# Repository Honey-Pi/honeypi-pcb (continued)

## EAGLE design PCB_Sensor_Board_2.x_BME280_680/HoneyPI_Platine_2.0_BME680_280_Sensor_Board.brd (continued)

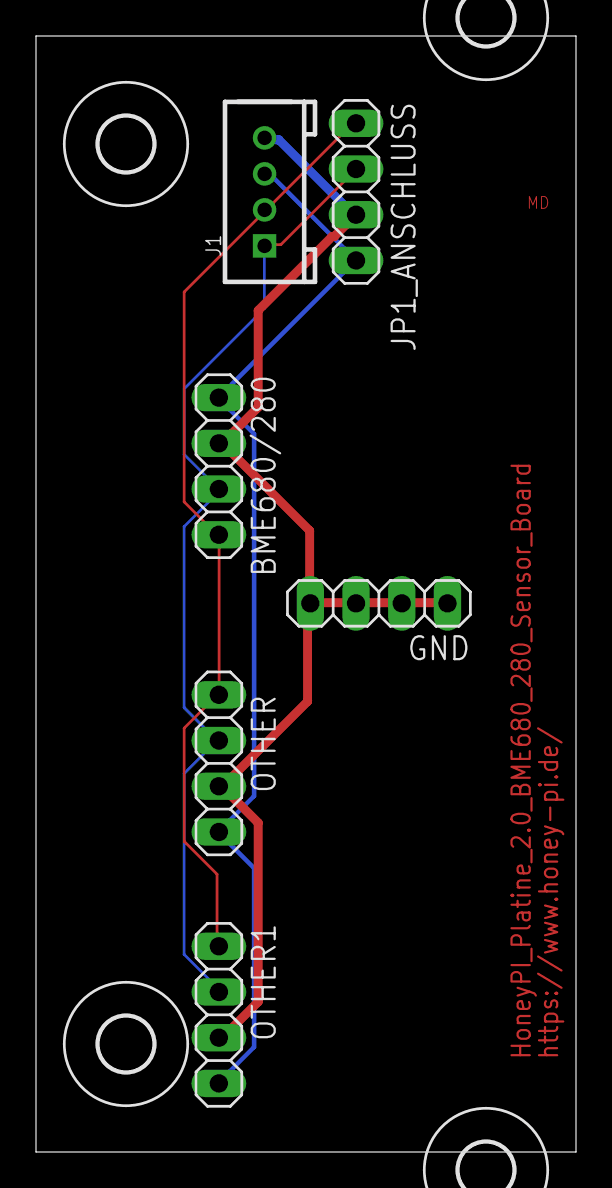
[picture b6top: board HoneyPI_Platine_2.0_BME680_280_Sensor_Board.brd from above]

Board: 2 copper layers, 30.0 x 62.0 mm, 10 parts (0 on the bottom side), 4 nets.

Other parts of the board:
U$1, U$2, U$3, U$4: 3,0

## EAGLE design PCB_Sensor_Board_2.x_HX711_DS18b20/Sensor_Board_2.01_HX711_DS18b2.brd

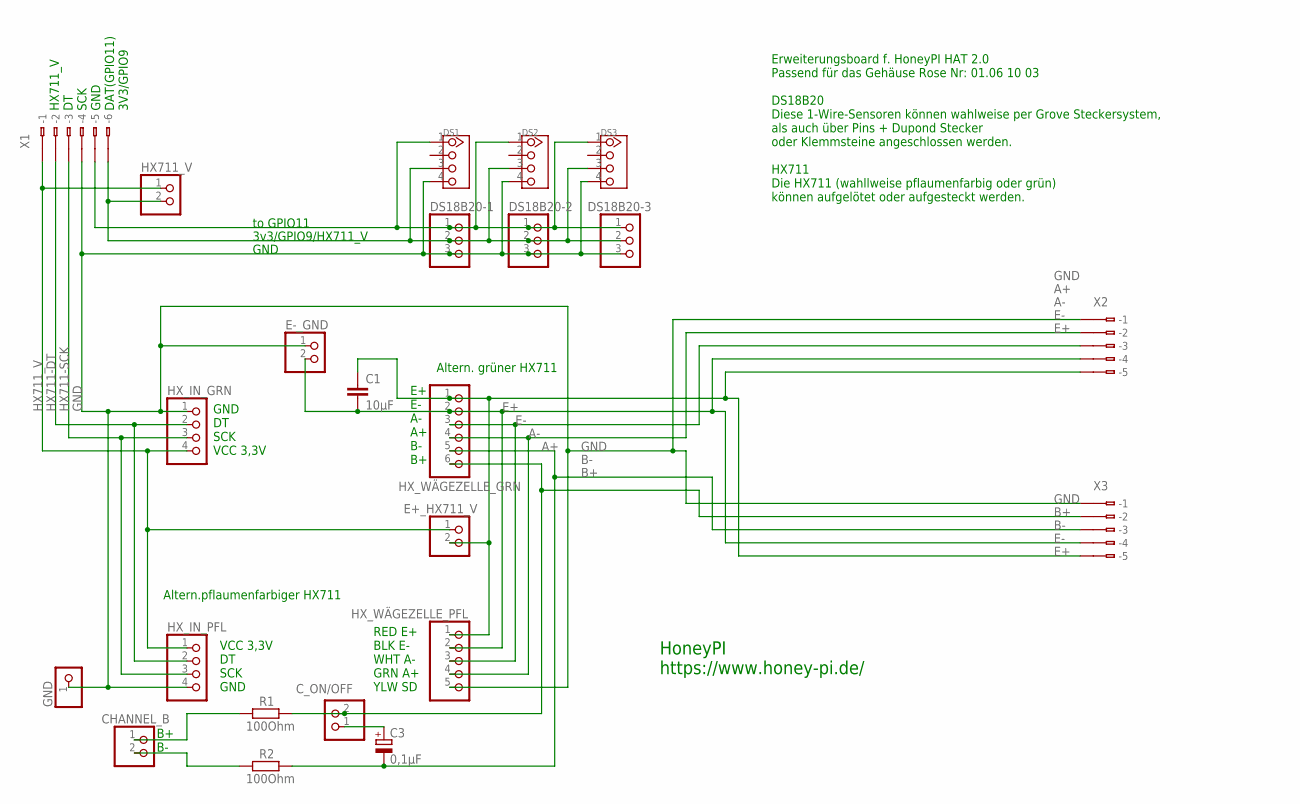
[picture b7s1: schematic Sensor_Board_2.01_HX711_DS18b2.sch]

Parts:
C1: 10µF; C5B2.5
C3: 0,1µF; E2,5-7
CHANNEL_B: PINHD-1X2; 1X02
C_ON/OFF: PINHD-1X2; 1X02
DS1, DS2, DS3: TWIG-4P-2.0-2.0; 4P-2.0
DS18B20-1, DS18B20-2, DS18B20-3: PINHD-1X3; 1X03
E+_HX711_V: PINHD-1X2; 1X02
E-_GND: PINHD-1X2; 1X02
GND: PINHD-1X1; 1X01
HX711_V: PINHD-1X2; 1X02
HX_IN_GRN: PINHD-1X4; 1X04
HX_IN_PFL: PINHD-1X4; 1X04
HX_WÄGEZELLE_GRN: PINHD-1X6; 1X06
HX_WÄGEZELLE_PFL: PINHD-1X5; 1X05
R1, R2: 100Ohm; 0207/10
X1: 233-506
X2, X3: 233-505

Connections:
3V3: DS1.3, DS2.3, DS3.3, DS18B20-1.2, DS18B20-2.2, DS18B20-3.2, HX711_V.2, X1.B6 (B-6)
A+: HX_WÄGEZELLE_GRN.4, HX_WÄGEZELLE_PFL.4, X2.B2 (B-2)
A-: HX_WÄGEZELLE_GRN.3, HX_WÄGEZELLE_PFL.3, X2.B3 (B-3)
B+: C_ON/OFF.2, HX_WÄGEZELLE_GRN.6, R1.2, X3.B2 (B-2)
B-: C3.-, HX_WÄGEZELLE_GRN.5, R2.2, X3.B3 (B-3)
DS18B20_DATA_GPIO11_PIN23: DS1.1, DS2.1, DS3.1, DS18B20-1.1, DS18B20-2.1, DS18B20-3.1, X1.B5 (B-5)
E+: C1.1, E+_HX711_V.2, HX_WÄGEZELLE_GRN.1, HX_WÄGEZELLE_PFL.1, X2.B5 (B-5), X3.B5 (B-5)
E-: C1.2, E-_GND.2, HX_WÄGEZELLE_GRN.2, HX_WÄGEZELLE_PFL.2, X2.B4 (B-4), X3.B4 (B-4)
GND: DS1.4, DS2.4, DS3.4, DS18B20-1.3, DS18B20-2.3, DS18B20-3.3, E-_GND.1, GND.1, HX_IN_GRN.1, HX_IN_PFL.4, HX_WÄGEZELLE_PFL.5, X1.B4 (B-4), X2.B1 (B-1), X3.B1 (B-1)
HX711-DT: HX_IN_GRN.2, HX_IN_PFL.2, X1.B2 (B-2)
HX711-SCK: HX_IN_GRN.3, HX_IN_PFL.3, X1.B3 (B-3)
HX711_V: E+_HX711_V.1, HX711_V.1, HX_IN_GRN.4, HX_IN_PFL.1, X1.B1 (B-1)
unnamed: CHANNEL_B.1, R1.1
unnamed: CHANNEL_B.2, R2.1
unnamed: C3.+, C_ON/OFF.1

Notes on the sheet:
3v3/GPIO9/HX711_V
VCC 3,3V DT SCK GND
GND DT SCK VCC 3,3V
GND
to GPIO11
Erweiterungsboard f. HoneyPI HAT 2.0 Passend für das Gehäuse Rose Nr: 01.06 10 03 DS18B20 Diese 1-Wire-Sensoren können wahlweise per Grove Steckersystem, als auch über Pins + Dupond Stecker oder Klemmsteine angeschlossen werden. HX711 Die HX711 (wahllweise pflaumenfarbig oder grün) können aufgelöte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
E+ E- A- A+ B- B+
RED E+ BLK E- WHT A- GRN A+ YLW SD
B+ B-
Altern.pflaumenfarbiger HX711
Altern. grüner HX711
HX711_V DT SCK GND DAT(GPIO11) 3V3/GPIO9
HoneyPI https://www.honey-pi.de/

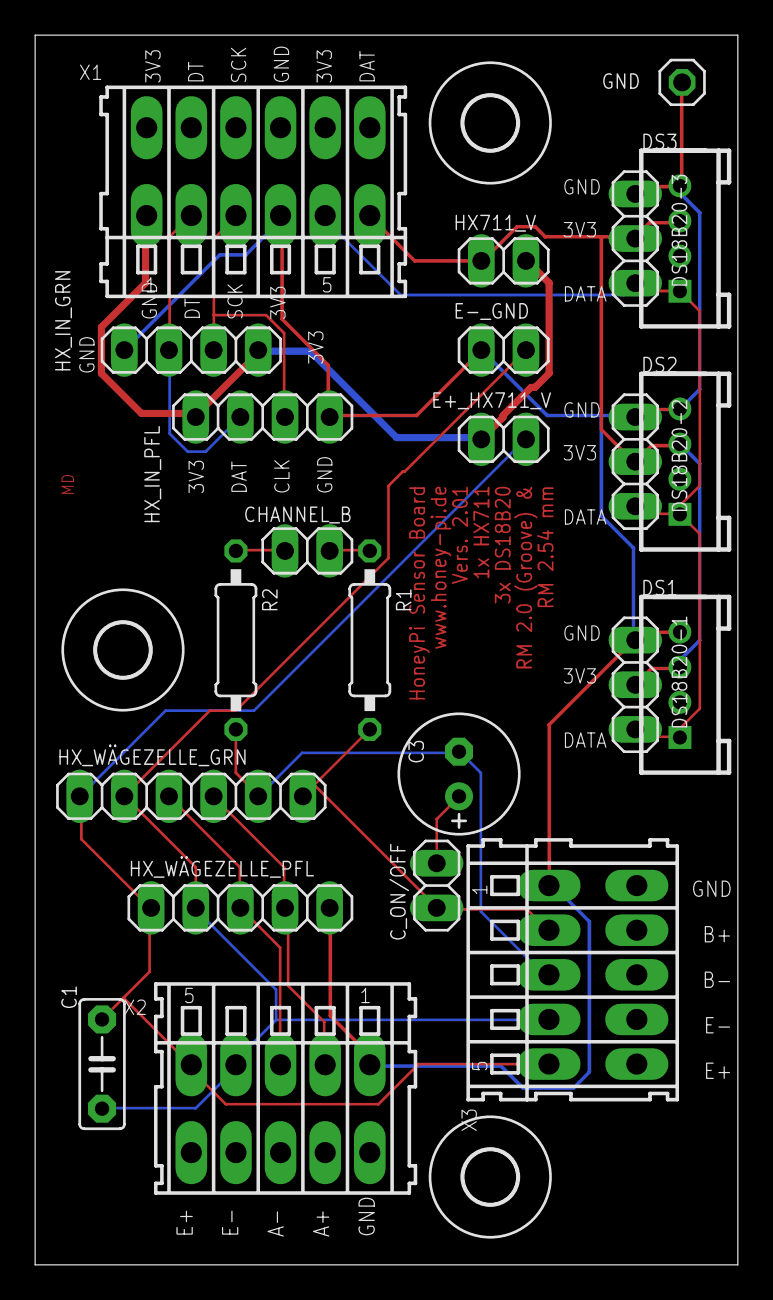
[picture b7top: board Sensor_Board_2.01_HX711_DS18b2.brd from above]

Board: 2 copper layers, 40.0 x 70.0 mm, 26 parts (0 on the bottom side), 15 nets.

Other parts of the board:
U$1, U$2, U$5: 3,0

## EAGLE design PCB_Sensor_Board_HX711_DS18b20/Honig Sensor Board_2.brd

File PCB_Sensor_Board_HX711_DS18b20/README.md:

# HoneyPi-PCB_Sensor_Board_HX711_DS18b20

Extension board for the HoneyPi-PCB 2.0. 
Pitch lenght 2.0 mm for Grove plugs or similar
Pitch lenght 2.54 mm for terminal blocks as an alternative
Designed to be mounted close to the load cell. To ensure that the analogue voltage signal is subject to the least interference.
Shielded cable to the load cell and aluminium housing are designed for this purpose. 
1x HX711
3x DS18b20

Feature list and bill of material is still on working. 

## V2.0 BETA circuit diagram [link](./HoneyPI_Platine%202.0%20Sensor%20Plan.pdf)
Check out this [blogpost](https://www.honey-pi.de/)

Status: Under development.
This version is currently being procured and tested.
Please do not order these without having contacted us before.
Thank you for your understanding!

You can upload this [gerber file] (./Gerber%20Honig%20Sensor%20Board_2_2020-05-03.zip) to [this manufactory service](https://jlcpcb.com/quote) to get few PCBs. 10 pieces of this board cost about 7 € with delivery. 

### Pictures

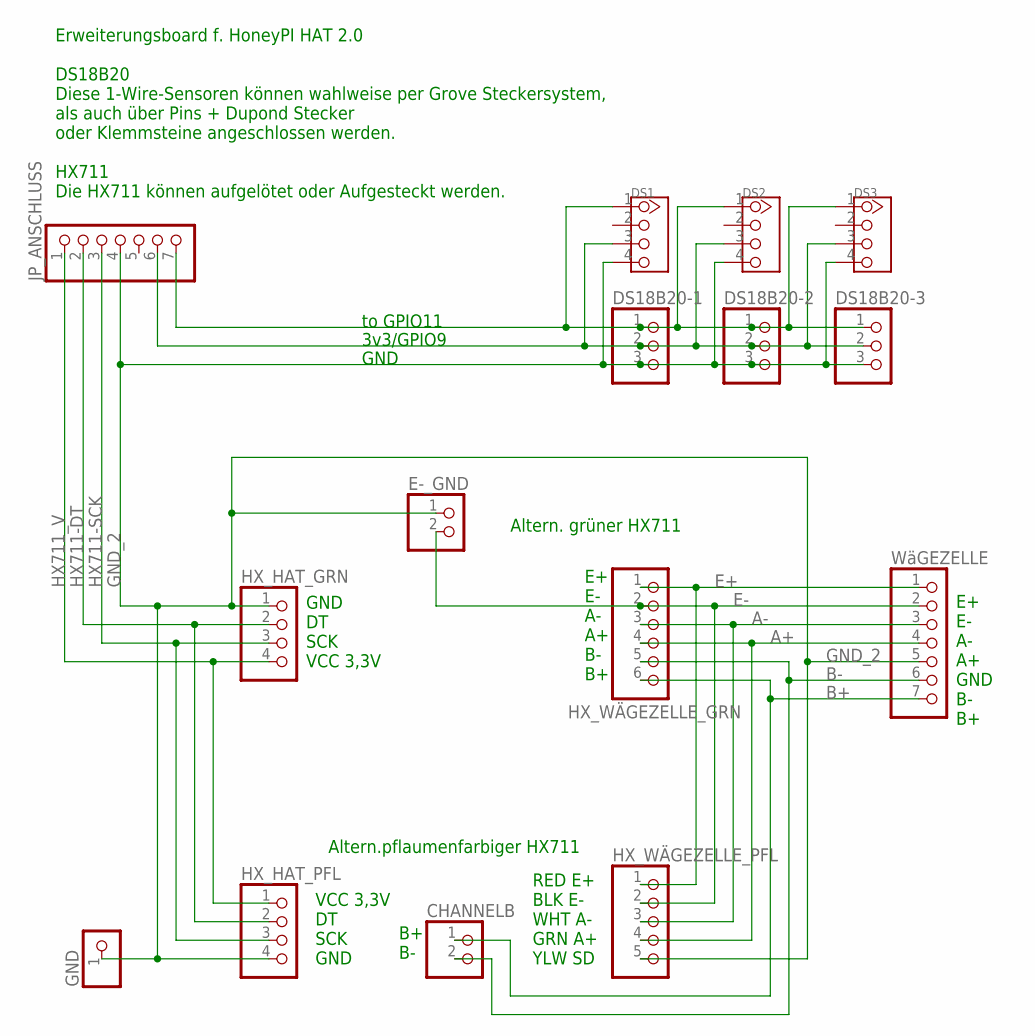
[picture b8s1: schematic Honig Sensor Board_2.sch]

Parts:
CHANNELB: PINHD-1X2; 1X02
DS1, DS2, DS3: TWIG-4P-2.0-2.0; 4P-2.0
DS18B20-1, DS18B20-2, DS18B20-3: PINHD-1X3; 1X03
E-_GND: PINHD-1X2; 1X02
GND: PINHD-1X1; 1X01
HX_HAT_GRN: PINHD-1X4; 1X04
HX_HAT_PFL: PINHD-1X4; 1X04
HX_WÄGEZELLE_GRN: PINHD-1X6; 1X06
HX_WÄGEZELLE_PFL: PINHD-1X5; 1X05
JP_ANSCHLUSS: PINHD-1X7; 1X07
WäGEZELLE: PINHD-1X7; 1X07

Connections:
3V3: DS1.3, DS2.3, DS3.3, DS18B20-1.2, DS18B20-2.2, DS18B20-3.2, JP_ANSCHLUSS.6
A+: HX_WÄGEZELLE_GRN.4, HX_WÄGEZELLE_PFL.4, WäGEZELLE.4
A-: HX_WÄGEZELLE_GRN.3, HX_WÄGEZELLE_PFL.3, WäGEZELLE.3
B+: CHANNELB.1, HX_WÄGEZELLE_GRN.6, WäGEZELLE.7
B-: CHANNELB.2, HX_WÄGEZELLE_GRN.5, WäGEZELLE.6
DS18B20_DATA_GPIO11_PIN23: DS1.1, DS2.1, DS3.1, DS18B20-1.1, DS18B20-2.1, DS18B20-3.1, JP_ANSCHLUSS.7
E+: HX_WÄGEZELLE_GRN.1, HX_WÄGEZELLE_PFL.1, WäGEZELLE.1
E-: E-_GND.2, HX_WÄGEZELLE_GRN.2, HX_WÄGEZELLE_PFL.2, WäGEZELLE.2
GND_2: DS1.4, DS2.4, DS3.4, DS18B20-1.3, DS18B20-2.3, DS18B20-3.3, E-_GND.1, GND.1, HX_HAT_GRN.1, HX_HAT_PFL.4, HX_WÄGEZELLE_PFL.5, JP_ANSCHLUSS.4, WäGEZELLE.5
HX711-DT: HX_HAT_GRN.2, HX_HAT_PFL.2, JP_ANSCHLUSS.2
HX711-SCK: HX_HAT_GRN.3, HX_HAT_PFL.3, JP_ANSCHLUSS.3
HX711_V: HX_HAT_GRN.4, HX_HAT_PFL.1, JP_ANSCHLUSS.1

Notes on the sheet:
3v3/GPIO9
VCC 3,3V DT SCK GND
GND DT SCK VCC 3,3V
GND
to GPIO11
Erweiterungsboard f. HoneyPI HAT 2.0 DS18B20 Diese 1-Wire-Sensoren können wahlweise per Grove Steckersystem, als auch über Pins + Dupond Stecker oder Klemmsteine angeschlossen werden. HX711 Die HX711 können aufgelötet oder Aufgesteckt werden.
E+ E- A- A+ B- B+
RED E+ BLK E- WHT A- GRN A+ YLW SD
B+ B-
Altern.pflaumenfarbiger HX711
Altern. grüner HX711
E+ E- A- A+ GND B- B+

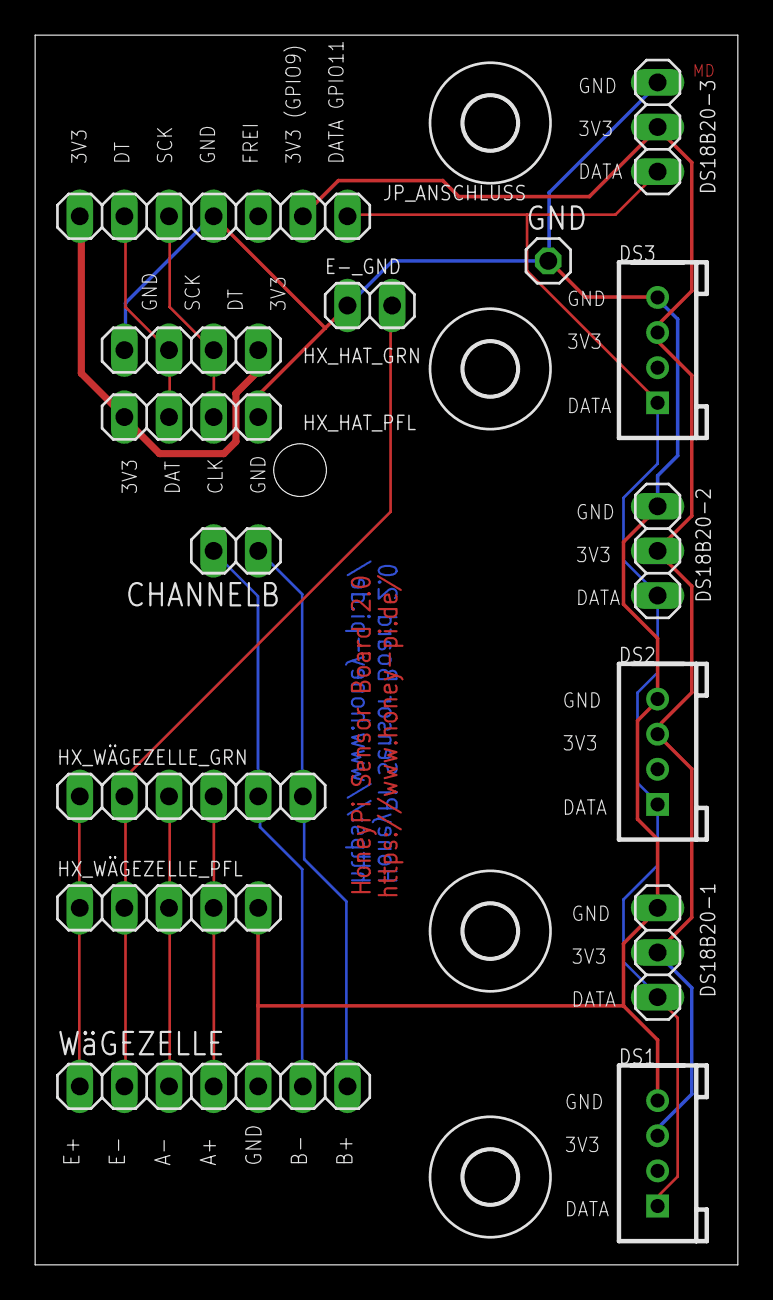
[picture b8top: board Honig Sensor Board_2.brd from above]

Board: 2 copper layers, 40.0 x 70.0 mm, 19 parts (0 on the bottom side), 12 nets.

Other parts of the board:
U$1, U$2, U$3, U$4: 3,0

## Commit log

2020-03-04 Initial commit of Version v0.1
2020-03-07 added picture
2020-05-06 test
2020-05-06 Beta 2.0:
    For purchasing and testing
2020-05-06 Beta
2020-05-18 Version added
2020-05-18 Correction 2.0 -> 2.01
    Correction of the pin description
2020-05-18 Correction 2.0 -> 2.01
    Correction of the pin description
    Moved: 2.0 to OLD
2020-05-19 Data sheets added
2020-05-20 Pictures of the components
2020-06-09 Pictures
2020-06-10 New version
2020-06-10 add_ 1x DS18B20 TO-92
2020-06-10 Text formatted
2020-06-10 only small changes :-)
2020-06-10 New circuit diagram
2020-06-21 Create LICENSE
2020-06-21 alpha status!
2020-06-30 3rd i²C interface
2020-06-30 2x Polyfuse
    The circuit has been extended by 2 optional polyfuses or similar. The fuse size has been accepted and not yet verified.
    Please note: The operator of the board must ensure safe operation. Accordingly, a fuse must be installed in accordance with the regulations.
2020-06-30 Switch for timer on/off
    switch for switching from time control to standard operation inserted
2020-08-21 Updates, updates....
2020-08-21 Updates, updates...
2020-08-21 Filenames corrected
2020-08-21 Update...
2020-08-21 Twisted pairs cable info
2020-09-27 Release
2020-09-27 Manual
2020-10-05 2019 --> 2020
2020-11-16 Gerber file produced with new CAM file and some small manual changes
2020-11-16 Gerber update
2020-11-16 Gerberfiles update
2020-12-19 jlcpcb_2_layer_v9.cam
    New cam file from JLCPCB.
    jlcpcb_2_layer_v9.cam
2020-12-19 _ instead of space in the file name of the gerber file
2021-01-05 New releases
    Fix BME680_GROVE Pinout on the main board
    Some corrections on the sensor board
2021-01-05 Data sheets and ordering examples
2021-01-11 Label corection (3V3 <-> DAT)
2021-01-19 fixed missing spaces
2021-01-19 updated to new folder name
2021-01-21 text correction
2021-02-03 Update documentation
2021-02-04 File named
2021-02-18 fixed layout
2021-02-18 cleaning: old files -> \old\
2021-02-20 Some printed parts
2021-03-27 Modem beta
2021-03-27 svg ->png
    Bad SVG export.
    SVG export was faulty. Therefore PNG
2021-04-15 several datasheets...
2021-05-04 updated Modem, added installer
2021-05-04 fix installer
2021-05-19 updated installer
2021-05-24 Upload datasheet BME680
2021-05-27 added ttyS0
2021-10-09 Update Link
2021-12-19 added Display instructions
2021-12-19 Ver. 2.04
    I2C address overview
    Sensor SHT20
2021-12-20 SHT20
2021-12-29 CJMCU-2317
2022-02-28 Datasheets
2022-04-01 Dok update
2022-04-13 alpha release (internal)
2022-04-29 Update Doc
2022-08-13 fix bme680_grove pinout
2022-08-15 Upload gerber files
2023-04-10 Pictures from the alpha pcb
2023-11-28 CH8_CH_8.5
    To fit more than on HX711 with slide different measure of the pins CH8 and CH_8.5
2024-03-26 Discontinued
2024-11-27 Update Bienenwaage_Platine_2.x_D2.07.pdf
    Links corrected
